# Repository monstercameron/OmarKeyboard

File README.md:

<div align="center">

[Current T4 keyboard assembly for SolidWorks](hardware/mechanical-rfq/rev-b2-t4/Omar-Keyboard-full-T4.step) · [USB-C carrier fabrication and assembly files](hardware/usb-c-carrier/README.md) · [Assembly specification](hardware/assembly-design-specification.md).

# Omar-Keyboard

**A keyboard made for [Omarchy](https://omarchy.org/).** Desks, windows and launchers get labeled keys of their own, arranged around a standard US layout.

[**Visit the site**](https://monstercameron.github.io/OmarKeyboard/) &nbsp;·&nbsp; [Try it in your browser](https://monstercameron.github.io/OmarKeyboard/#try) &nbsp;·&nbsp; [Explore the circuit board](https://monstercameron.github.io/OmarKeyboard/#circuit) &nbsp;·&nbsp; [Configure the firmware](https://monstercameron.github.io/OmarKeyboard/#configure)

</div>

## What it does

Omarchy runs on keyboard shortcuts. Omar-Keyboard puts the most-used ones on keys that say what they do, so you don't need to remember a chord.

- **Five desk keys** above the number row. Tap **Desk 3** to go there. Press **Send & Stay**, then **Desk 3**, to move the window and keep working where you are.
- **Launchers on the left edge.** Terminal, Browser, Files, Guide and Menu each have a key. Menu sits at home-row height.
- **Window controls on the right edge.** Hold **Focus** or **Swap** and press an arrow to move between tiles. Float, Fullscreen and Flip Split have keys of their own.
- **A wide roller** in place of the navigation block. Pull it toward you to scroll down. Hold Fn while rolling to move a page at a time.
- **Two dials.** The left one sets volume and mutes when pressed. The right one sets brightness.
- **A light under every key.** The 90 per-key lights show the active desk, a muted microphone and Caps Lock.

The typing block is an ordinary US QWERTY layout, with the full number row, two Super keys and a Ctrl key on either side. The included Omarchy profile defaults to five desktops per monitor. Caps works as Fn when held. The [full keymap](docs/design/keymap.md) covers alternate legends and cancelling a move.

## A tour of the site

[The site](https://monstercameron.github.io/OmarKeyboard/) walks through the keyboard one part at a time. The 3D board turns as you scroll, and hand-drawn notes point out the parts worth a look. Each picture below links to its section.

### [Try it](https://monstercameron.github.io/OmarKeyboard/#try)

Press the keys on the board and a simulated Omarchy screen above it responds. Send a window to Desk 3, follow it, or hold Focus and press an arrow. What you type goes to the focused terminal. The [full-screen prototype](https://monstercameron.github.io/OmarKeyboard/prototype/OMAR-KEYBOARD-PROTOTYPE.html) can also print the layout at full size, so you can check reach on paper.

### [The print model](https://monstercameron.github.io/OmarKeyboard/#print)

The T4 assembly the prints are made from, exported from SolidCraft with every legend modeled as raised geometry. The site loads a 5-million-triangle copy, 10.8 MB, only when you press **Load the print model**. Then you can turn it, zoom in on the legends, or jump to the roller and the front edge.

### [The circuit board](https://monstercameron.github.io/OmarKeyboard/#circuit)

The routed Rev B.1 board is drawn from the KiCad files, with the top copper in orange and the bottom in blue. Pulses follow the USB data and the light chain. Hand-drawn notes mark where USB comes in, where the 90 lights start and where the controller sits. Choose a part to zoom to it.

### [Controller pins and schematics](https://monstercameron.github.io/OmarKeyboard/#mcu-title)

The RP2040 is shown from above, with all 56 pins labeled. Choose a group or point at a pin to see where it goes. Beside it are the 14 schematic sheets, six of them for the lights.

### [A light under every key](https://monstercameron.github.io/OmarKeyboard/#lights)

Each of the 90 keys has an SK6812MINI-E under it. Switch between the states the board shows: the active desk in cyan, a pending move, Caps Lock, a muted microphone and a held Focus key. The brightness controls show the current the whole board would draw.

### [Parts and what the board needs](https://monstercameron.github.io/OmarKeyboard/#parts)

The table lists all 403 parts with their package, their side of the board and what each one does. Prices for the encoders, lights and sockets come from the JLCPCB quote, and the rest are estimates. **Show** zooms the board drawing to that part.

### [Configure the firmware](https://monstercameron.github.io/OmarKeyboard/#configure)

Choose a key to see its keycode, its place in the switch matrix and what Omarchy receives. Change assignments, tapping term and brightness, then copy the generated `keymap.c`, `config.h`, `rules.mk` and `keymap.json`. A board running VIA can be read and written over USB.

### [Where it's heading](https://monstercameron.github.io/OmarKeyboard/#roadmap)

The roadmap is drawn like a trace on the board. Solid steps are done, and the dashed ones still have to be routed. The rear USB-C carrier is routed. Its plating, assembly and service fit await supplier confirmation and first-article tests.

## Current prototype hardware

| Part | B.2 mainboard, T3 roller and T4 USB-C carrier |
| --- | --- |
| Controller | RP2040 reading an 8 × 12 key matrix, with USB-C at the rear |
| Switches | 89 Gateron G Pro 3.0 Brown, and a Cherry MX Grey for Lock |
| Dials | Two Bourns PEC11R encoders with 24 detents |
| Lights | 90 SK6812MINI-E per-key LEDs on one chain, starting at Esc. A load switch turns the light rail off. |
| Power | Estimated 292 mA at default white and 393 mA at the 16/255 ceiling. First-article target ≤450 mA at the host |
| Board | 405 placements, including the two roller pull-ups. Native KiCad DRC passes. |
| Cost | The historical B.1 quote was $277.81 for five 403-placement boards. B.2 needs a fresh quote. |
| Firmware | QMK, target `omar_keyboard/rev_b` |

The current hardware pairs a 405-placement Rev B.2 mainboard with a separate soldered roller card and T3 mechanical assembly. The four-layer T4 USB-C carrier completes the three-board set. All three native DRC reports pass. Card, harness and screw fit have been checked in CAD. A populated physical sample remains to be tested. [Rev B.2 board](hardware/mainboard-rev-b2/README.md) · [Encoder card](hardware/roller-encoder-card/README.md) · [T3 roller assembly](hardware/mechanical-rfq/rev-b2-t3/README.md)

### Drawings

These drawings come from the [assembly design specification](hardware/assembly-design-specification.md).

<p>

</p>

## Try it yourself

- **In a browser.** The [Try it section](https://monstercameron.github.io/OmarKeyboard/#try) and the [full-screen prototype](https://monstercameron.github.io/OmarKeyboard/prototype/OMAR-KEYBOARD-PROTOTYPE.html) run with nothing to install. In the prototype, try **Send & Stay** and then **Move & Go** with the same desk to compare them. **Print full-size fit template** prints the layout at true scale. Measure both 100 mm bars on the printout before you judge the fit.
- **In 3D.** The [site](https://monstercameron.github.io/OmarKeyboard/#inside) shows the outside and the internal assembly. The [offline viewer](hardware/model/View-Omar-Keyboard.html) works without a network connection. The [Blender assembly](hardware/model/Omar-Keyboard.blend) and the [GLB](docs/assets/omar-keyboard.glb) are editable.
- **On a keyboard you already own.** The [build pilot](docs/build/pilot.md) maps the controls onto an existing QMK board. The [Omarchy bindings](host/omarchy/) target Omarchy v4.5.0.
- **With your own keymap.** The [firmware configurator](https://monstercameron.github.io/OmarKeyboard/#configure) writes a `keymap.c` you can compile with QMK.

To run the site locally, serve `docs/` from the repository root:

```sh
python -m http.server 8000 --bind 127.0.0.1 --directory docs
```

Then open `http://127.0.0.1:8000/`.

## Inside the repository

| To do this | Start here |
| --- | --- |
| Build or review the full assembly | [Assembly design specification](hardware/assembly-design-specification.md) · [Illustrated PDF](hardware/assembly-design-specification.pdf) |
| Open the current T3 plate and roller | [Positioned STEP, revised parts and fit checks](hardware/mechanical-rfq/rev-b2-t3/README.md) |
| Review the earlier T2 quotations | [STEP assembly, part drawings and plate quotations](hardware/mechanical-rfq/rev-b1-t2/README.md) |
| Order or review the Rev B.1 board | [KiCad project, BOM and quotes](hardware/mainboard-rev-b/README.md) · [Rev B firmware](firmware/qmk/omar_keyboard/rev_b/) |
| Look at the earlier Rev A board | [Rev A mainboard](hardware/mainboard/README.md) · [Verification report](hardware/mainboard/verification.md) · [Rev A firmware](firmware/qmk/omar_keyboard/rev_a/) |
| Check dimensions, switch positions or parts | [Hardware specification](hardware/specification.md) · [Parts and cost plan](hardware/parts-plan.md) · [Switch coordinates](hardware/layout/omar-switches.csv) · [Dimensioned drawing](docs/assets/omar-dimensions.svg) |
| See inside the case | [Internal assembly](hardware/model/internals/README.md) · [Offline internal viewer](hardware/model/internals/View-Internals.html) · [Tray STL](hardware/model/Omar-Keyboard-Tray.stl) |
| Print the case and keycaps | [T4 print files](hardware/mechanical-rfq/rev-b2-t4/README.md) · [One-piece tray STL](hardware/mechanical-rfq/rev-b2-t4/T4-One-piece-tray.stl) · [High-detail print model, GLB](docs/assets/omar-print-model.glb) |
| Run a reach or usability session | [Validation tasks and acceptance criteria](docs/design/validation.md) |
| Understand the design decisions | [Omarchy interaction patterns](docs/research/omarchy.md) · [Stock shortcuts](docs/research/stock-shortcuts.md) · [Keyboard market study](docs/research/keyboards.md) · [Controllers and firmware](docs/research/controllers.md) |
| Change the layout, model or site | [Contributor and verification guide](CONTRIBUTING.md) |
| See how the design started | [First layout](archive/first-layout.md) · [Earlier drafts](archive/earlier-drafts/) |

## License

The original code, hardware designs and documentation are released under the [MIT License](LICENSE). The bundled 3D viewer runtime has its own license, listed in the [third-party notices](THIRD_PARTY_NOTICES.md).

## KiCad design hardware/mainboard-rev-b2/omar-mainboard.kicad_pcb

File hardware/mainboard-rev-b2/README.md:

# Omar-Keyboard mainboard Rev B.2

[Populated B.2 STEP](omar-mainboard-populated.step) includes all 405 installed references. [T4 full assembly and interference checks](../mechanical-rfq/rev-b2-t4/README.md).

Rev B.2 adds two independent roller encoder pull-ups to the routed 90-LED RP2040 board. It uses the same three-wire J2 pinout and existing Rev B QMK target. The historical B.1 supplier price covers 403 placements. B.2 has 405 placements and needs its own price and first-article test.

| Reference | Connection | Footprint centre in board coordinates | Side |
| --- | --- | --- | --- |
| R12 | +3V3 to ROLL_A, J2.1 and GP24 | X366.90 Y52.80 | Front |
| R13 | +3V3 to ROLL_B, J2.3 and GP25 | X352.50 Y44.10 | Back |

Both parts are UNI-ROYAL 0603WAF2701T5E, 2.7 kΩ ±1%, 0603, 100 mW. The resistor alone supplies 1.22 mA at 3.30 V through a closed contact. J2.2 is common ground. On a populated board measure both closed-contact currents against 1–10 mA and confirm clean logic transitions and 30 scroll events per turn in each direction. [Resistor listing](https://jlcpcb.com/partdetail/C13167) · [Encoder rating](https://tech.alpsalpine.com/e/products/detail/EC11E15204A3/)

KiCad 7.0.11 reports zero DRC violations, unconnected pads and footprint errors. The schematic and PCB agree on all 1,082 connected pad assignments. The assembly BOM and CPL contain the same 405 distinct references. Both new placement centres, rotations and sides match the native placement export. The R13 bottom-side and R12 top-side fit envelopes appear in the roller STEP.

[KiCad project](omar-mainboard.kicad_pro) · [Schematic](omar-mainboard.kicad_sch) · [Routed PCB](omar-mainboard.kicad_pcb) · [DRC report](drc-report.txt)

[Gerbers and drills](omar-mainboard-Gerbers.zip) · [JLCPCB BOM](JLCPCB-BOM.csv) · [JLCPCB CPL](JLCPCB-CPL.csv) · [Purchasing BOM](purchasing-bom.csv) · [Roller card](../roller-encoder-card/README.md) · [Positioned assembly](../mechanical-rfq/rev-b2-t3/README.md)

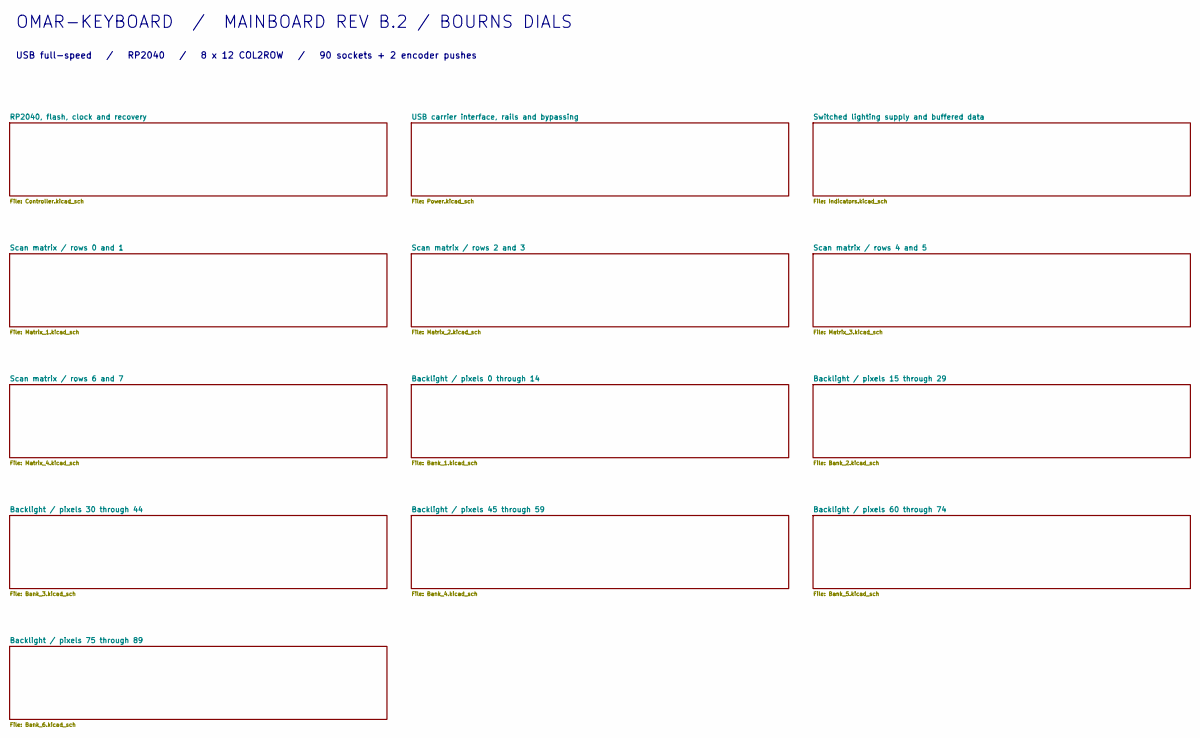
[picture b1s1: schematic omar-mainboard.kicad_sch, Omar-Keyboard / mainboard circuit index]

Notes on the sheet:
OMAR-KEYBOARD / MAINBOARD REV B.2 / BOURNS DIALS
USB full-speed / RP2040 / 8 x 12 COL2ROW / 90 sockets + 2 encoder pushes

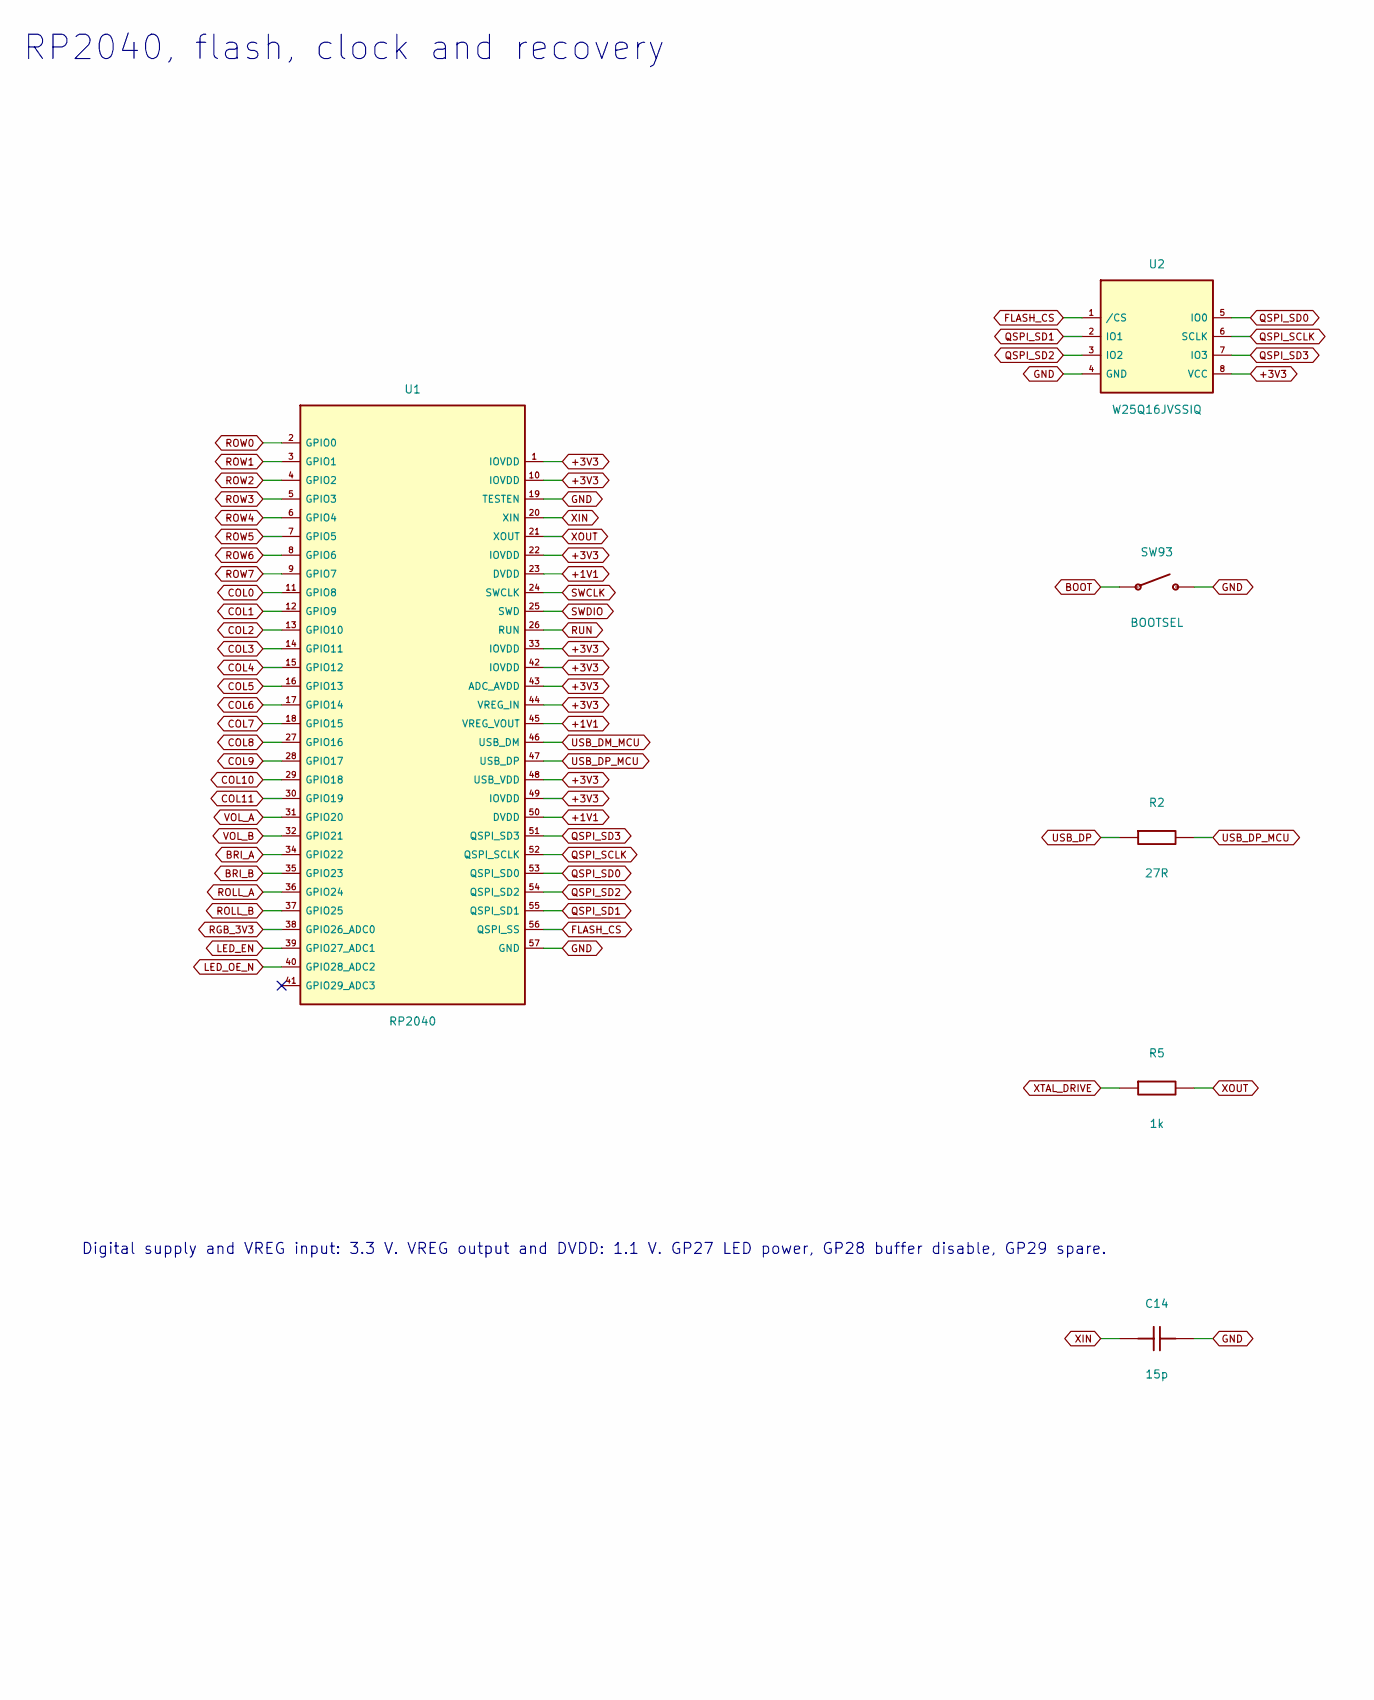
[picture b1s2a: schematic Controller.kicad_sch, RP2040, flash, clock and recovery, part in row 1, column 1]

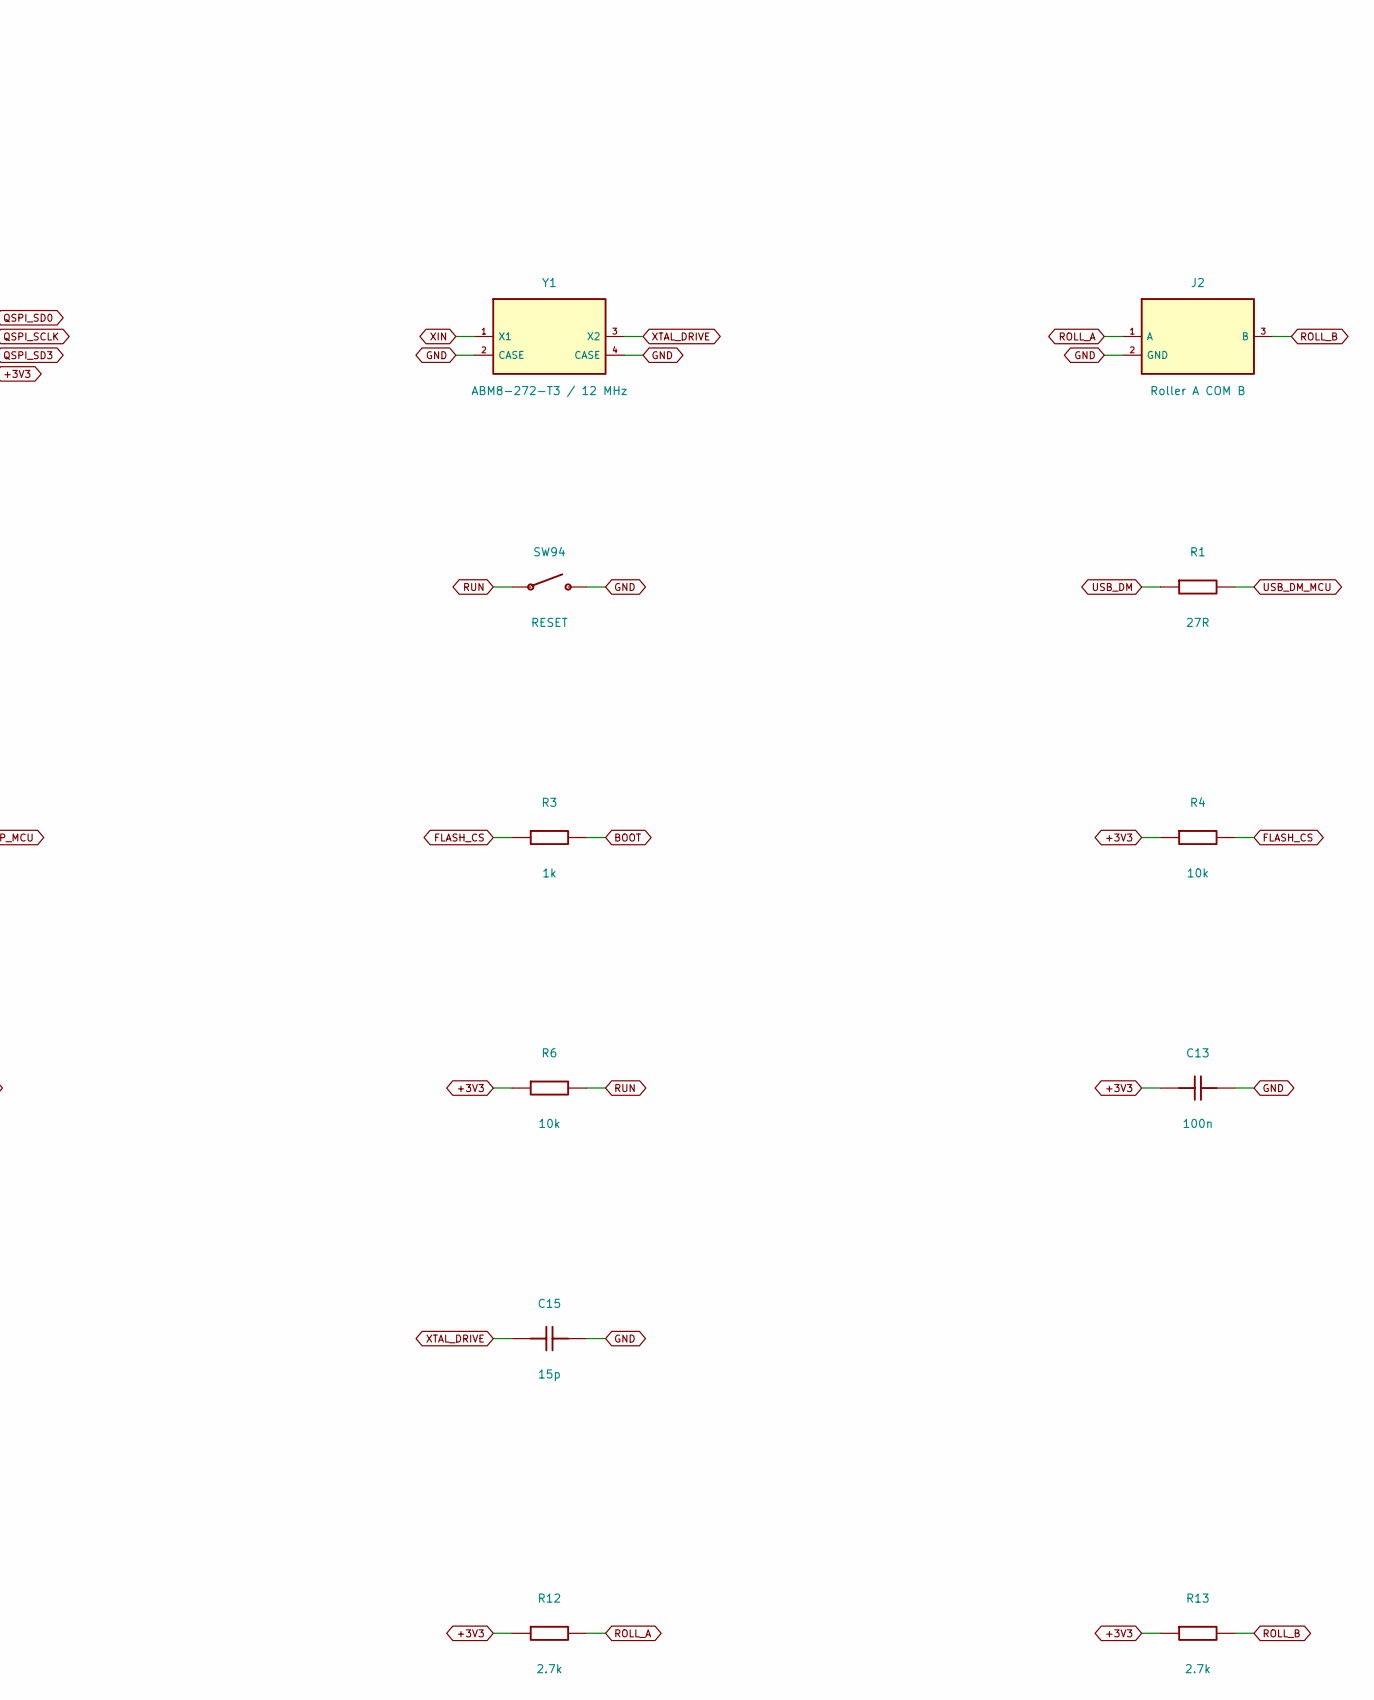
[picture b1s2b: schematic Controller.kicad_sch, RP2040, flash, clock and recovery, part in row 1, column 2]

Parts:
C13: 100n; C_0603_1608Metric
C14, C15: 15p; C_0603_1608Metric
J2: Roller A COM B; Wire_3_P1.5
R1, R2: 27R; R_0603_1608Metric
R3, R5: 1k; R_0603_1608Metric
R4, R6: 10k; R_0603_1608Metric
R12, R13: 2.7k; R_0603_1608Metric
SW93: BOOTSEL; SW_SPST_PTS810
SW94: RESET; SW_SPST_PTS810
U1: RP2040; QFN-56-1EP_7x7mm_P0.4mm_EP3.2x3.2mm
U2: W25Q16JVSSIQ; SOIC-8W_5.3x5.3mm_P1.27mm
Y1: ABM8-272-T3 / 12 MHz; Crystal_SMD_3225-4Pin_3.2x2.5mm

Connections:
+1V1: U1.23 (DVDD), U1.45 (VREG_VOUT), U1.50 (DVDD); also elsewhere on the board
+3V3: C13.1, R4.1, R6.1, R12.1, R13.1, U1.1 (IOVDD), U1.10 (IOVDD), U1.22 (IOVDD), U1.33 (IOVDD), U1.42 (IOVDD), U1.43 (ADC_AVDD), U1.44 (VREG_IN), U1.48 (USB_VDD), U1.49 (IOVDD), U2.8 (VCC); also elsewhere on the board
BOOT: R3.2, SW93.1
BRI_A: U1.34 (GPIO22); also elsewhere on the board
BRI_B: U1.35 (GPIO23); also elsewhere on the board
COL0: U1.11 (GPIO8); also elsewhere on the board
COL1: U1.12 (GPIO9); also elsewhere on the board
COL2: U1.13 (GPIO10); also elsewhere on the board
COL3: U1.14 (GPIO11); also elsewhere on the board
COL4: U1.15 (GPIO12); also elsewhere on the board
COL5: U1.16 (GPIO13); also elsewhere on the board
COL6: U1.17 (GPIO14); also elsewhere on the board
COL7: U1.18 (GPIO15); also elsewhere on the board
COL8: U1.27 (GPIO16); also elsewhere on the board
COL9: U1.28 (GPIO17); also elsewhere on the board
COL10: U1.29 (GPIO18); also elsewhere on the board
COL11: U1.30 (GPIO19); also elsewhere on the board
FLASH_CS: R3.1, R4.2, U1.56 (QSPI_SS), U2.1 (/CS)
GND: C13.2, C14.2, C15.2, J2.2 (GND), SW93.2, SW94.2, U1.19 (TESTEN), U1.57 (GND), U2.4 (GND), Y1.2 (CASE), Y1.4 (CASE); also elsewhere on the board
LED_EN: U1.39 (GPIO27_ADC1); also elsewhere on the board
LED_OE_N: U1.40 (GPIO28_ADC2); also elsewhere on the board
QSPI_SCLK: U1.52 (QSPI_SCLK), U2.6 (SCLK)
QSPI_SD0: U1.53 (QSPI_SD0), U2.5 (IO0)
QSPI_SD1: U1.55 (QSPI_SD1), U2.2 (IO1)
QSPI_SD2: U1.54 (QSPI_SD2), U2.3 (IO2)
QSPI_SD3: U1.51 (QSPI_SD3), U2.7 (IO3)
RGB_3V3: U1.38 (GPIO26_ADC0); also elsewhere on the board
ROLL_A: J2.1 (A), R12.2, U1.36 (GPIO24)
ROLL_B: J2.3 (B), R13.2, U1.37 (GPIO25)
ROW0: U1.2 (GPIO0); also elsewhere on the board
ROW1: U1.3 (GPIO1); also elsewhere on the board
ROW2: U1.4 (GPIO2); also elsewhere on the board
ROW3: U1.5 (GPIO3); also elsewhere on the board
ROW4: U1.6 (GPIO4); also elsewhere on the board
ROW5: U1.7 (GPIO5); also elsewhere on the board
ROW6: U1.8 (GPIO6); also elsewhere on the board
ROW7: U1.9 (GPIO7); also elsewhere on the board
RUN: R6.2, SW94.1, U1.26 (RUN)
SWCLK: U1.24 (SWCLK); also elsewhere on the board
SWDIO: U1.25 (SWD); also elsewhere on the board
USB_DM: R1.1; also elsewhere on the board
USB_DM_MCU: R1.2, U1.46 (USB_DM)
USB_DP: R2.1; also elsewhere on the board
USB_DP_MCU: R2.2, U1.47 (USB_DP)
VOL_A: U1.31 (GPIO20); also elsewhere on the board
VOL_B: U1.32 (GPIO21); also elsewhere on the board
XIN: C14.1, U1.20 (XIN), Y1.1 (X1)
XOUT: R5.2, U1.21 (XOUT)
XTAL_DRIVE: C15.1, R5.1, Y1.3 (X2)

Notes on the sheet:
RP2040, flash, clock and recovery
Digital supply and VREG input: 3.3 V. VREG output and DVDD: 1.1 V. GP27 LED power, GP28 buffer disable, GP29 spare.

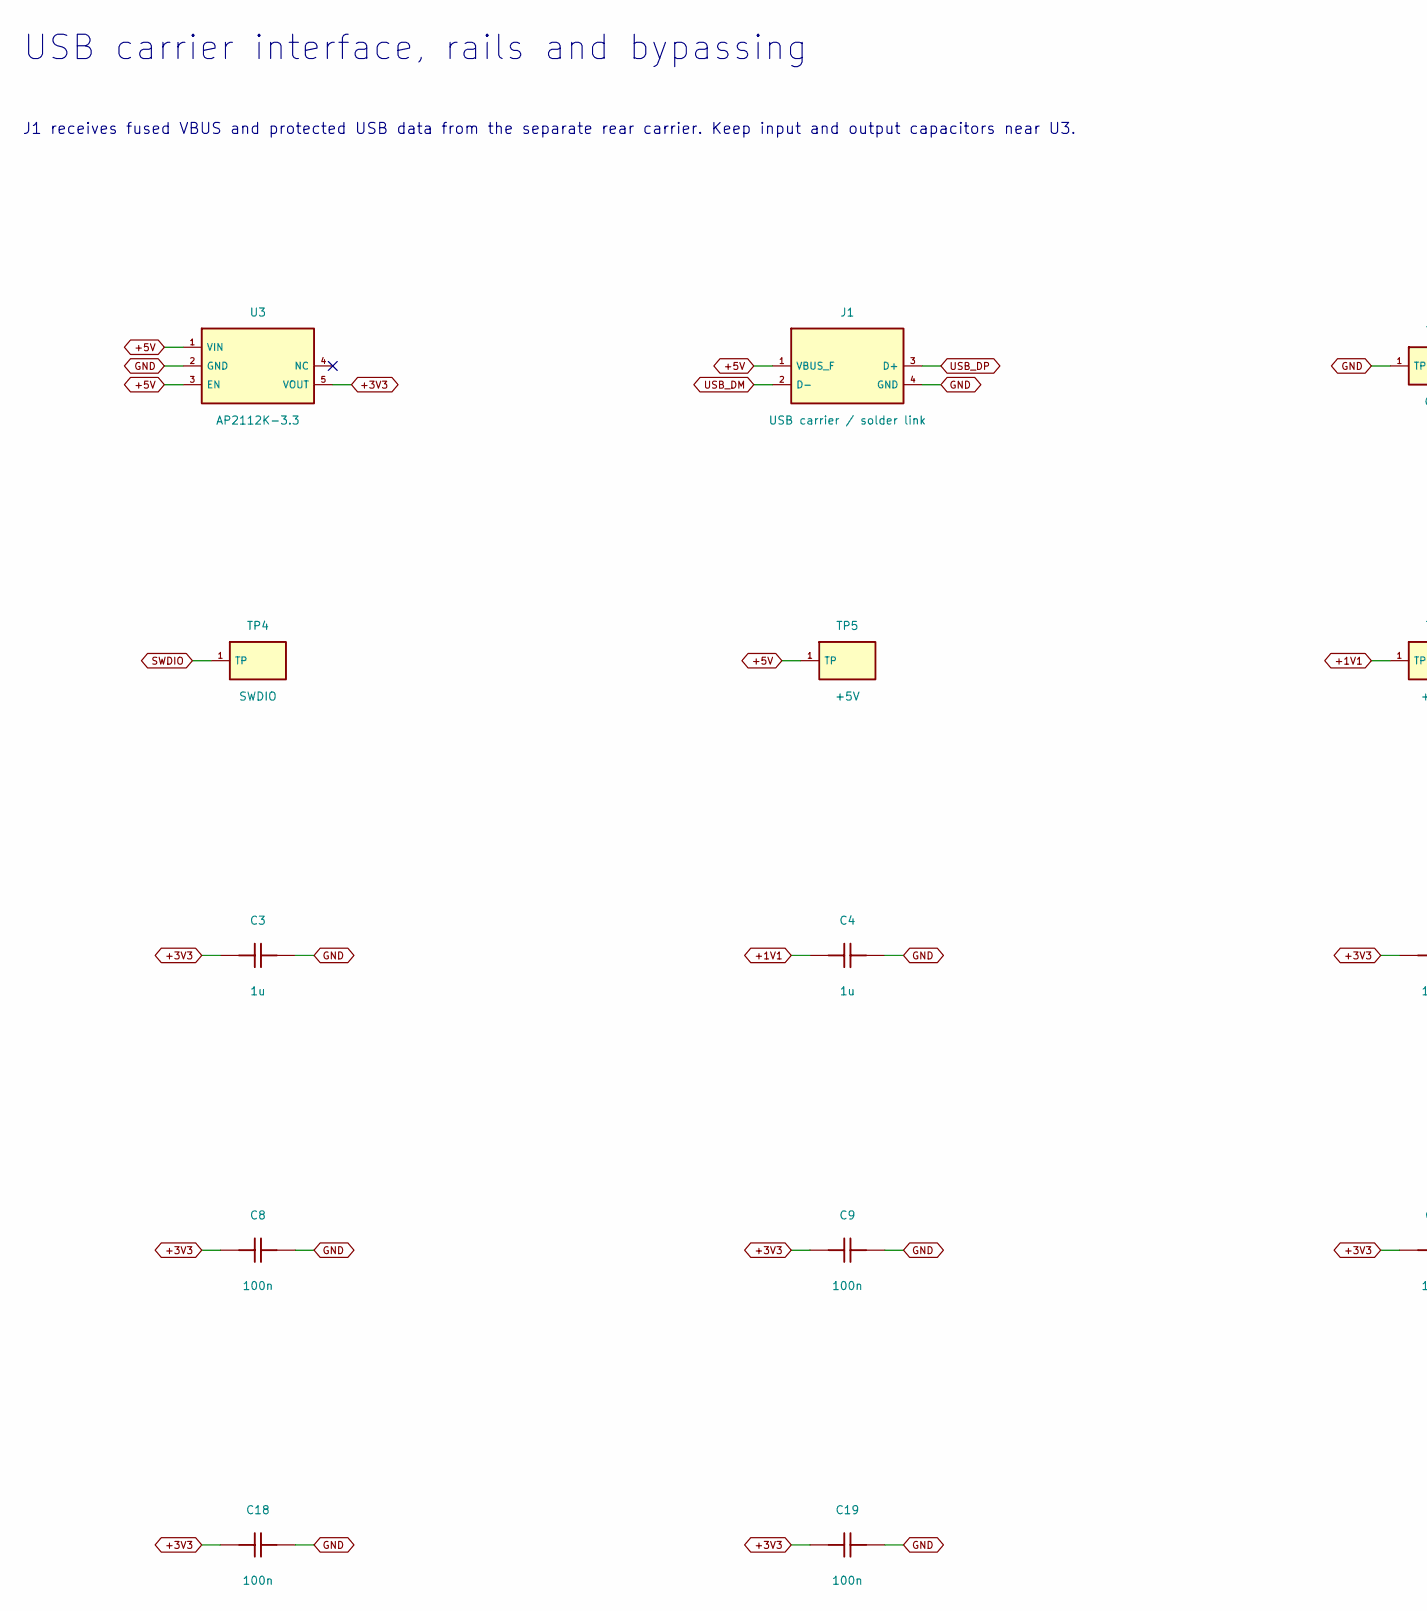
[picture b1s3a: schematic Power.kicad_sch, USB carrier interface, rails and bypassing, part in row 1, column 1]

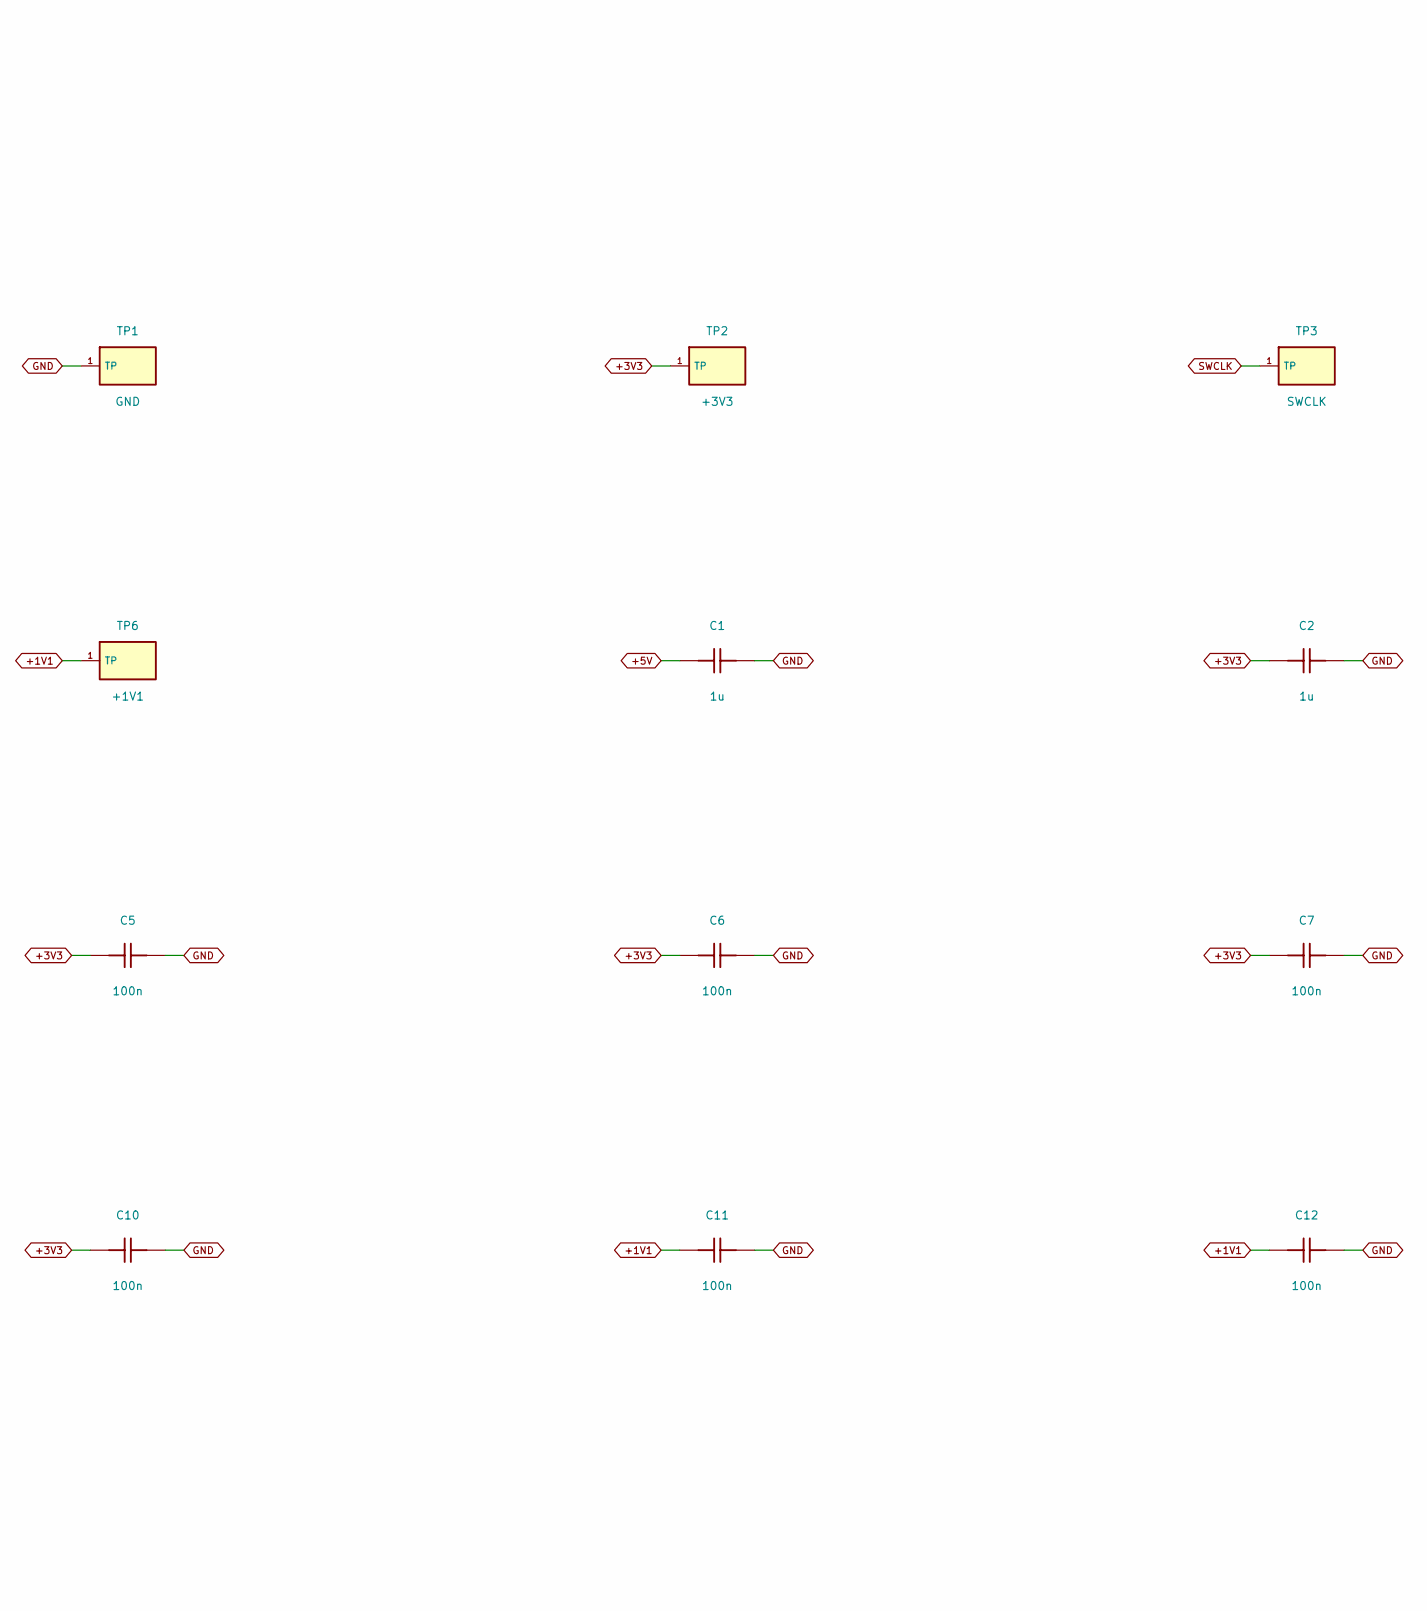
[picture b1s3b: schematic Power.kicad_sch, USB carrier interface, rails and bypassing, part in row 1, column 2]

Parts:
C1, C2, C3, C4: 1u; C_0603_1608Metric
C5, C6, C7, C8, C9, C10, C11, C12, C18, C19: 100n; C_0603_1608Metric
J1: USB carrier / solder link; Wire_4_P1.5
TP1: GND; TestPoint_Pad_D1.0mm
TP2: +3V3; TestPoint_Pad_D1.0mm
TP3: SWCLK; TestPoint_Pad_D1.0mm
TP4: SWDIO; TestPoint_Pad_D1.0mm
TP5: +5V; TestPoint_Pad_D1.0mm
TP6: +1V1; TestPoint_Pad_D1.0mm
U3: AP2112K-3.3; SOT-23-5

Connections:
+1V1: C4.1, C11.1, C12.1, TP6.1; also elsewhere on the board
+3V3: C2.1, C3.1, C5.1, C6.1, C7.1, C8.1, C9.1, C10.1, C18.1, C19.1, TP2.1, U3.5 (VOUT); also elsewhere on the board
+5V: C1.1, J1.1 (VBUS_F), TP5.1, U3.1 (VIN), U3.3 (EN); also elsewhere on the board
GND: C1.2, C2.2, C3.2, C4.2, C5.2, C6.2, C7.2, C8.2, C9.2, C10.2, C11.2, C12.2, C18.2, C19.2, J1.4 (GND), TP1.1, U3.2 (GND); also elsewhere on the board
SWCLK: TP3.1; also elsewhere on the board
SWDIO: TP4.1; also elsewhere on the board
USB_DM: J1.2 (D-); also elsewhere on the board
USB_DP: J1.3 (D+); also elsewhere on the board

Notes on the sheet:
USB carrier interface, rails and bypassing
J1 receives fused VBUS and protected USB data from the separate rear carrier. Keep input and output capacitors near U3.

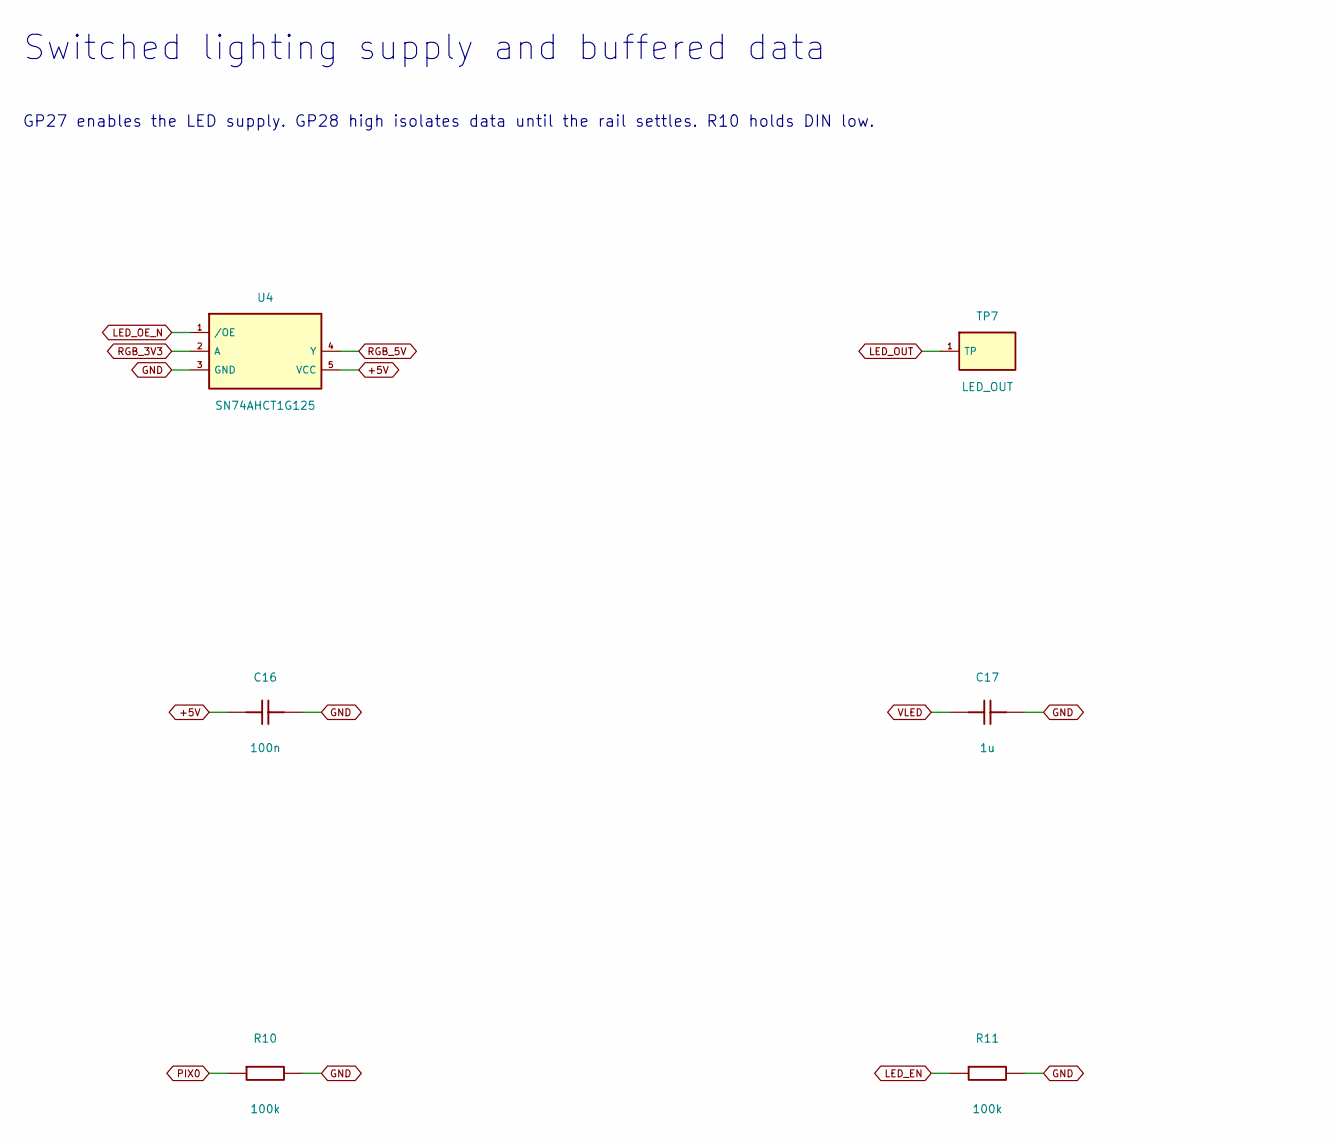
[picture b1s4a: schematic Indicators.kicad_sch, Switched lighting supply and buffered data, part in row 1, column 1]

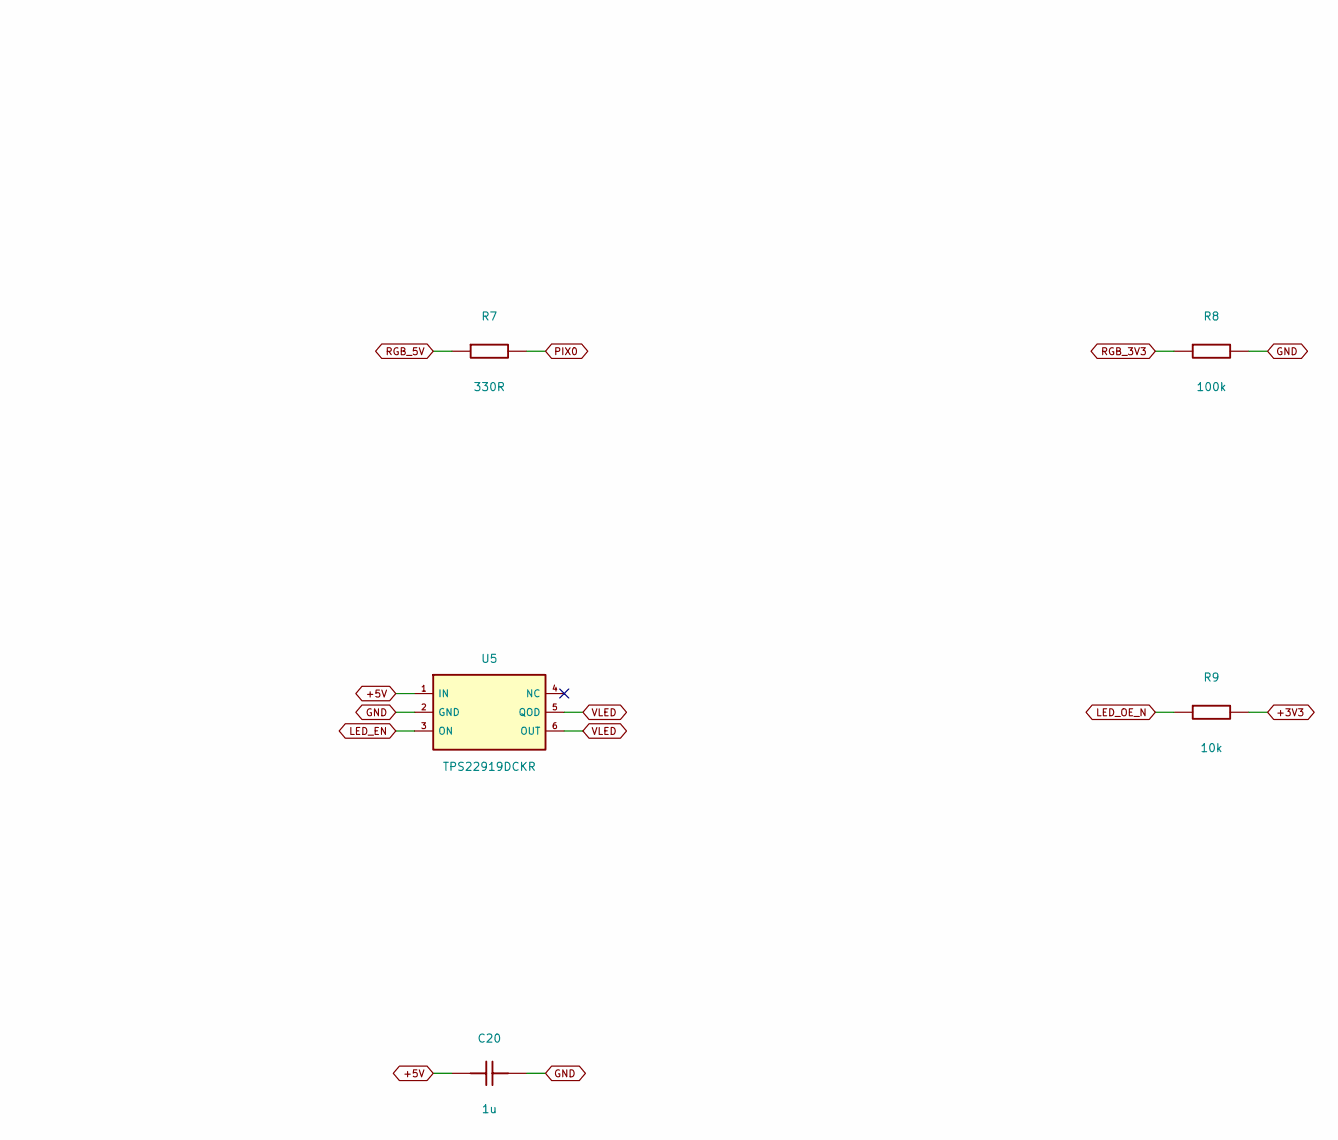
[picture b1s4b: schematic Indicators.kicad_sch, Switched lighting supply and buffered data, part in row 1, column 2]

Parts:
C16: 100n; C_0603_1608Metric
C17, C20: 1u; C_0603_1608Metric
R7: 330R; R_0603_1608Metric
R8, R10, R11: 100k; R_0603_1608Metric
R9: 10k; R_0603_1608Metric
TP7: LED_OUT; TestPoint_Pad_D1.0mm
U4: SN74AHCT1G125; SOT-23-5
U5: TPS22919DCKR; SOT-363_SC-70-6

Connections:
+3V3: R9.2; also elsewhere on the board
+5V: C16.1, C20.1, U4.5 (VCC), U5.1 (IN); also elsewhere on the board
GND: C16.2, C17.2, C20.2, R8.2, R10.2, R11.2, U4.3 (GND), U5.2 (GND); also elsewhere on the board
LED_EN: R11.1, U5.3 (ON); also elsewhere on the board
LED_OE_N: R9.1, U4.1 (/OE); also elsewhere on the board
LED_OUT: TP7.1; also elsewhere on the board
PIX0: R7.2, R10.1; also elsewhere on the board
RGB_3V3: R8.1, U4.2 (A); also elsewhere on the board
RGB_5V: R7.1, U4.4 (Y)
VLED: C17.1, U5.5 (QOD), U5.6 (OUT); also elsewhere on the board

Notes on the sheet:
Switched lighting supply and buffered data
GP27 enables the LED supply. GP28 high isolates data until the rail settles. R10 holds DIN low.
